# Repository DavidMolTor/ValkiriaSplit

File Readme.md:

# VALKIRIA SPLIT

Completely wireless, split mechanical keyboard based on the nRF52840 microcontroller, with independent wireless operation for each half.

## Introduction

This is a personal project born from my interest in exploring the world of ergonomic mechanical keyboards. After looking at several existing designs, I found that none of them offered exactly what I was looking for, so I decided to design and build my own.

I took a bit of a gamble by choosing a Corne-inspired layout without a dedicated number row, opting for a more minimal design. However, if I find that this layout does not suit my needs, I plan to develop a new version with additional keys.

## Features

 - Completely wireless operation of both sides.

 - Rechargeable and replaceable battery.

 - Hot-swappable chocolate sockets.

 - Full RGB with switchable regulator.

 - Two 1.08" MIP displays.

 - Rotary encoders with push button.

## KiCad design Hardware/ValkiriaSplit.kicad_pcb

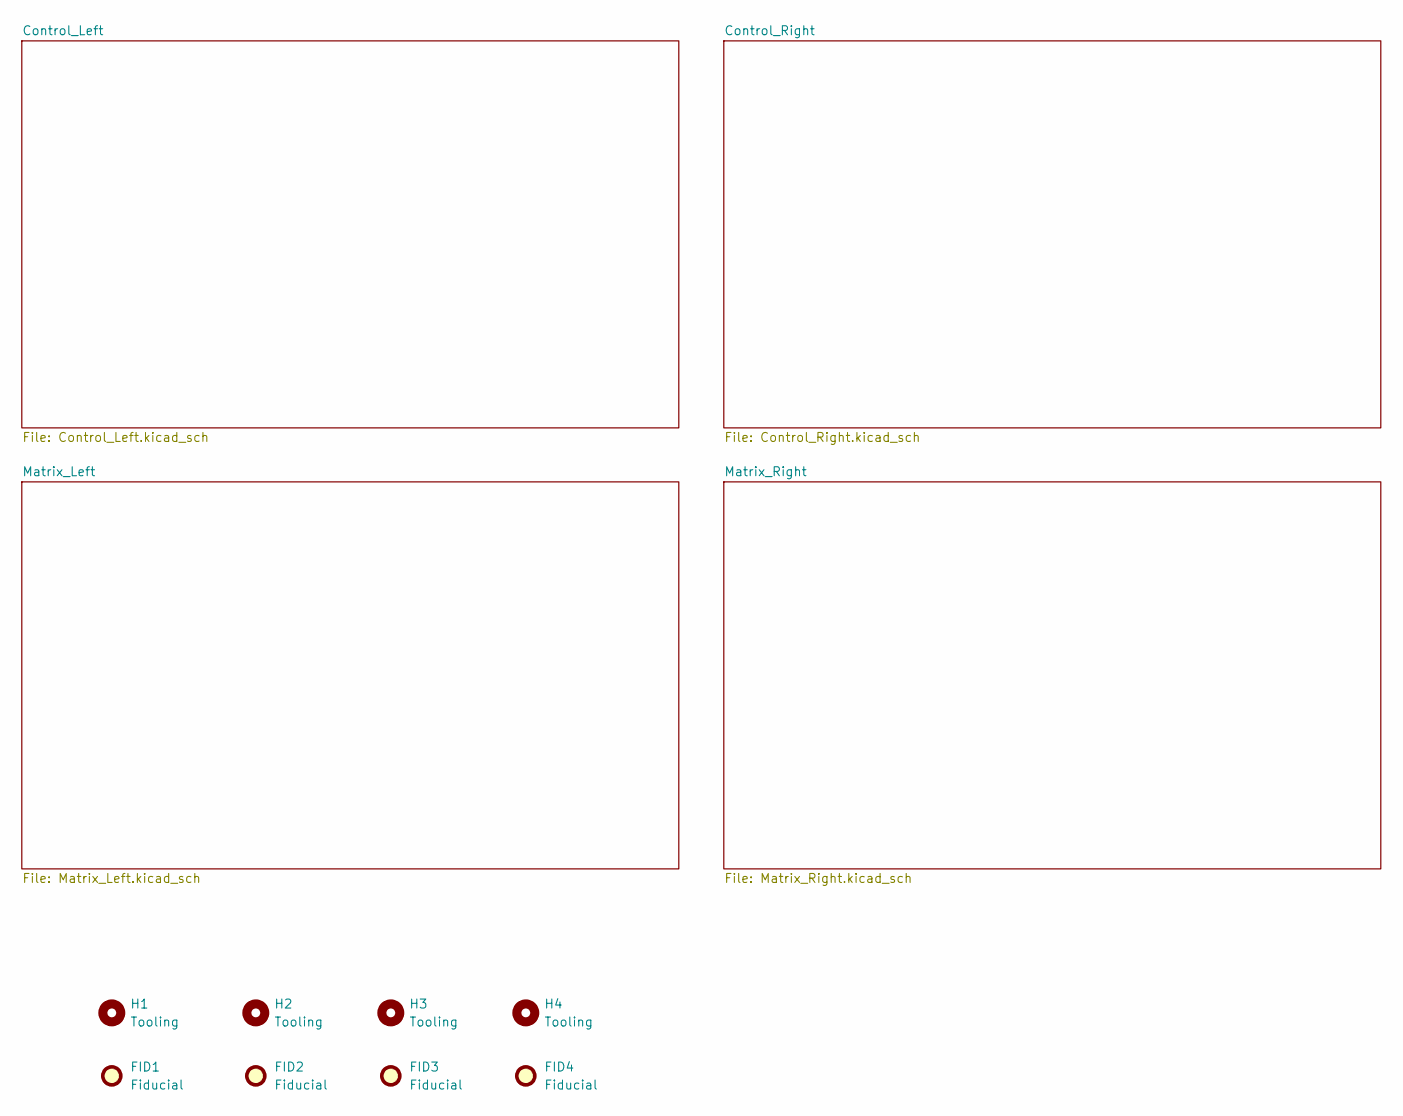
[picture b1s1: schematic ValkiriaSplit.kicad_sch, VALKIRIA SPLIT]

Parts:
FID1, FID2, FID3, FID4: Fiducial; Fiducial_1mm_Mask2mm
H1, H2, H3, H4: Tooling; ToolingHole_1.152mm

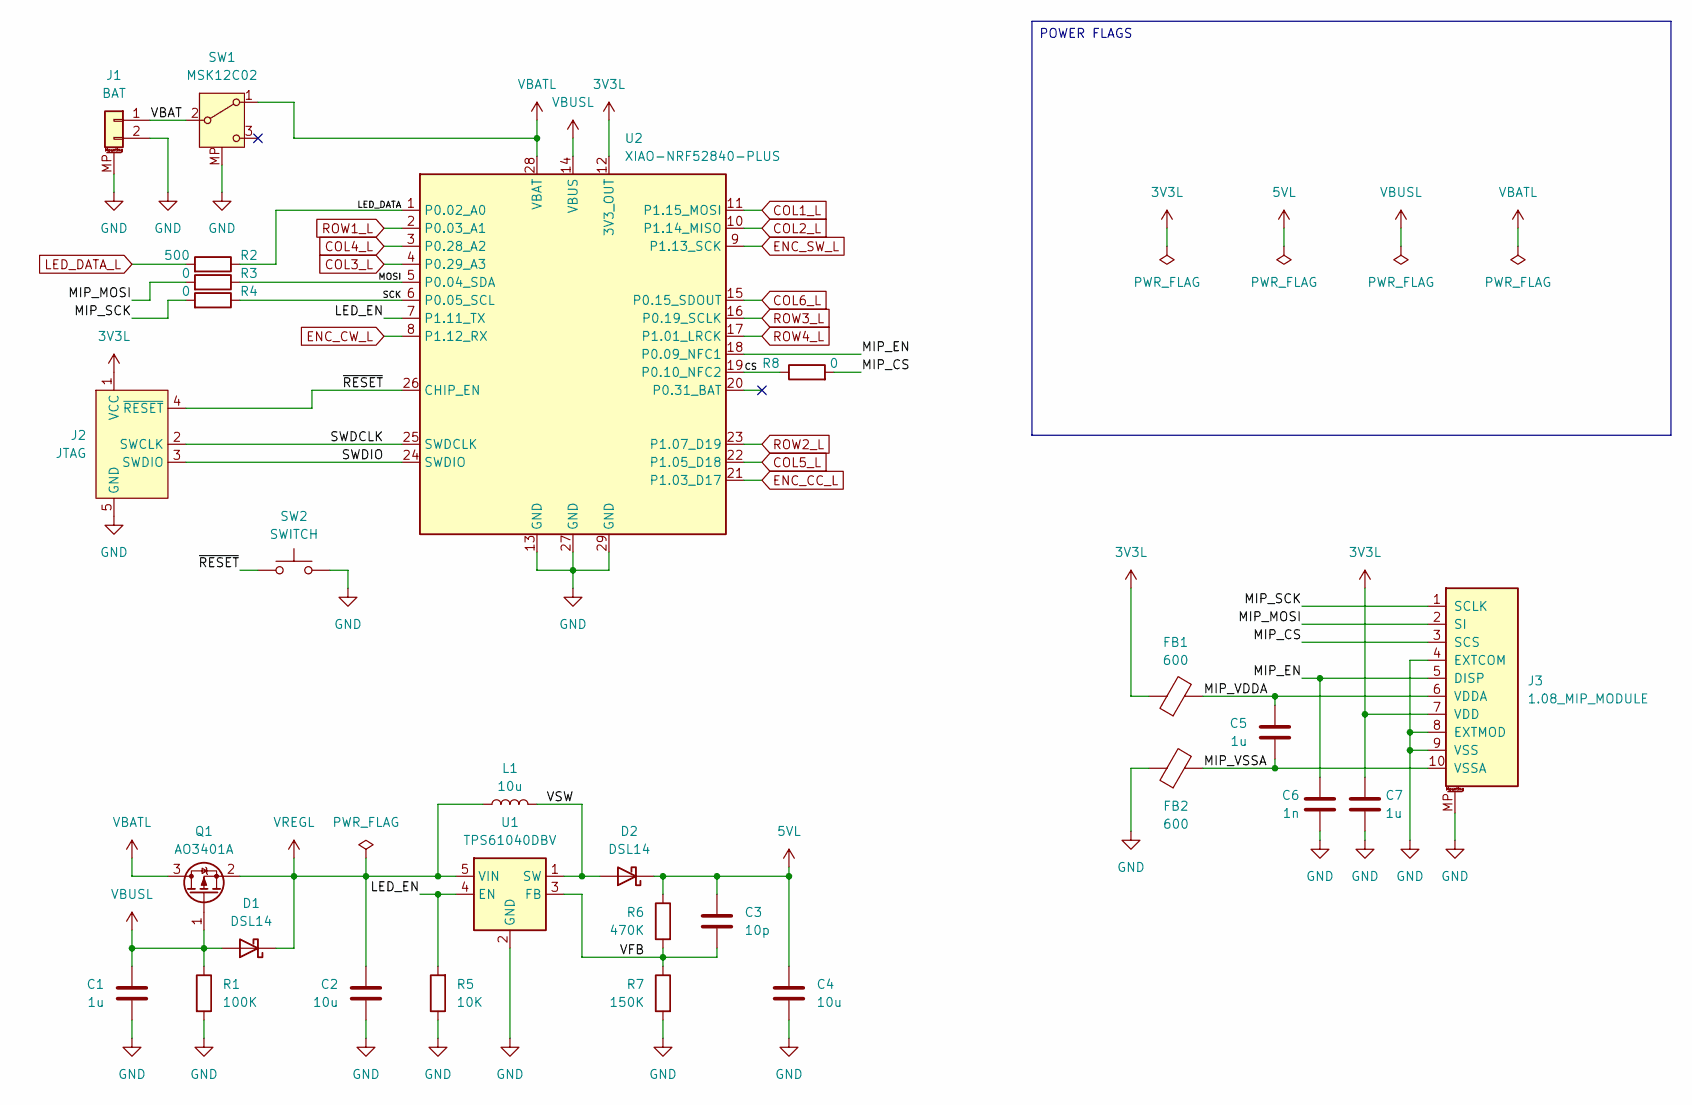
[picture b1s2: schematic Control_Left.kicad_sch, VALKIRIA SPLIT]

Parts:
C1, C5, C7: 1u; C_0603_1608Metric; Manufacturer Part CL10A105KB8NNNC; JLC Part C15849
C2, C4: 10u; C_0603_1608Metric; Manufacturer Part CL10A106MA8NRNC; JLC Part C96446
C3: 10p; C_0603_1608Metric; Manufacturer Part CL10C100JB8NNNC; JLC Part C1634
C6: 1n; C_0603_1608Metric; Manufacturer Part CL10B102KB8NNNC; JLC Part C1588
D1, D2: DSL14; D_SOD-123F; Manufacturer Part DSL14; JLC Part C22466349
FB1, FB2: 600; L_0603_1608Metric; Manufacturer Part GZ1608D601TF; JLC Part C1002
J1: BAT; JST_ZH_1x02_P1.50MM_SMD_HORIZONTAL; Manufacturer Part ZH1.5-2P-WT; JLC Part C722913
J2: JTAG; JTAG_SWD_1X05_1.27MM_COMBO
J3: 1.08_MIP_MODULE; 1.08_MIP_MODULE_TALL; Manufacturer Part AFC07-S10FCC-00; JLC Part C11050
L1: 10u; VLCF4020_MIRROR; Manufacturer Part NRS4018T100MDGJ; JLC Part C222882
Q1: AO3401A; SOT-23; Manufacturer Part AO3401A; JLC Part C15127
R1: 100K; R_0603_1608Metric; Manufacturer Part 0603WAF1003T5E; JLC Part C25803
R2: 500; R_0603_1608Metric; Manufacturer Part 0603WAF0000T5E; JLC Part C21189
R3, R4, R8: 0; R_0603_1608Metric; Manufacturer Part 0603WAF0000T5E; JLC Part C21189
R5: 10K; R_0603_1608Metric; Manufacturer Part 0603WAF1002T5E; JLC Part 0603WAF1002T5E
R6: 470K; R_0603_1608Metric; Manufacturer Part 0603WAF4703T5E; JLC Part C23178
R7: 150K; R_0603_1608Metric; Manufacturer Part 0603WAF1503T5E; JLC Part C22807
SW1: MSK12C02; Manufacturer Part MSK12C02-HB; JLC Part C431541
SW2: SWITCH; SW_SPST_TS-1088-xR020; Manufacturer Part TS-1088-AR02016; JLC Part C720477
U1: TPS61040DBV; SOT-23-5; Manufacturer Part TPS61040DBVR; JLC Part C7722
U2: XIAO-NRF52840-PLUS; XIAO-NRF52840-PLUS-SMD-EDGE

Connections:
3V3L: C7.1, FB1.1, J2.1 (VCC), J3.7 (VDD), U2.12 (3V3_OUT)
5VL: C3.1, C4.1, D2.1 (K), R6.1; also elsewhere on the board
/Control_Left/CS: R8.1, U2.19 (P0.10_NFC2)
/Control_Left/LED_DATA: R2.1, U2.1 (P0.02_A0)
/Control_Left/LED_EN: R5.2, U1.4 (EN), U2.7 (P1.11_TX)
/Control_Left/MIP_CS: J3.3 (SCS), R8.2
/Control_Left/MIP_EN: C6.1, J3.5 (DISP), U2.18 (P0.09_NFC1)
/Control_Left/MIP_MOSI: J3.2 (SI), R3.2
/Control_Left/MIP_SCK: J3.1 (SCLK), R4.2
/Control_Left/MIP_VDDA: C5.1, FB1.2, J3.6 (VDDA)
/Control_Left/MIP_VSSA: C5.2, FB2.2, J3.10 (VSSA)
/Control_Left/MOSI: R3.1, U2.5 (P0.04_SDA)
/Control_Left/SCK: R4.1, U2.6 (P0.05_SCL)
/Control_Left/SWDCLK: J2.2 (SWCLK), U2.25 (SWDCLK)
/Control_Left/SWDIO: J2.3 (SWDIO), U2.24 (SWDIO)
/Control_Left/VBAT: J1.1, SW1.2 (B)
/Control_Left/VFB: C3.2, R6.2, R7.1, U1.3 (FB)
/Control_Left/VSW: D2.2 (A), L1.2, U1.1 (SW)
/Control_Left/~RESET: J2.4 (~RESET), SW2.1, U2.26 (CHIP_EN)
COL1_L: U2.11 (P1.15_MOSI); also elsewhere on the board
COL2_L: U2.10 (P1.14_MISO); also elsewhere on the board
COL3_L: U2.4 (P0.29_A3); also elsewhere on the board
COL4_L: U2.3 (P0.28_A2); also elsewhere on the board
COL5_L: U2.22 (P1.05_D18); also elsewhere on the board
COL6_L: U2.15 (P0.15_SDOUT); also elsewhere on the board
ENC_CC_L: U2.21 (P1.03_D17); also elsewhere on the board
ENC_CW_L: U2.8 (P1.12_RX); also elsewhere on the board
ENC_SW_L: U2.9 (P1.13_SCK); also elsewhere on the board
GND: C1.2, C2.2, C4.2, C6.2, C7.2, FB2.1, J1.2, J1.MP (MountPin), J2.5 (GND), J3.4 (EXTCOM), J3.8 (EXTMOD), J3.9 (VSS), J3.MP, R1.2, R5.1, R7.2, SW1.MP, SW2.2, U1.2 (GND), U2.13 (GND), U2.27 (GND), U2.29 (GND); also elsewhere on the board
LED_DATA_L: R2.2; also elsewhere on the board
ROW1_L: U2.2 (P0.03_A1); also elsewhere on the board
ROW2_L: U2.23 (P1.07_D19); also elsewhere on the board
ROW3_L: U2.16 (P0.19_SCLK); also elsewhere on the board
ROW4_L: U2.17 (P1.01_LRCK); also elsewhere on the board
VBATL: Q1.3 (D), SW1.1 (A), U2.28 (VBAT)
VBUSL: C1.1, D1.2 (A), Q1.1 (G), R1.1, U2.14 (VBUS)
VREGL: C2.1, D1.1 (K), L1.1, Q1.2 (S), U1.5 (VIN)

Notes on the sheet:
POWER FLAGS

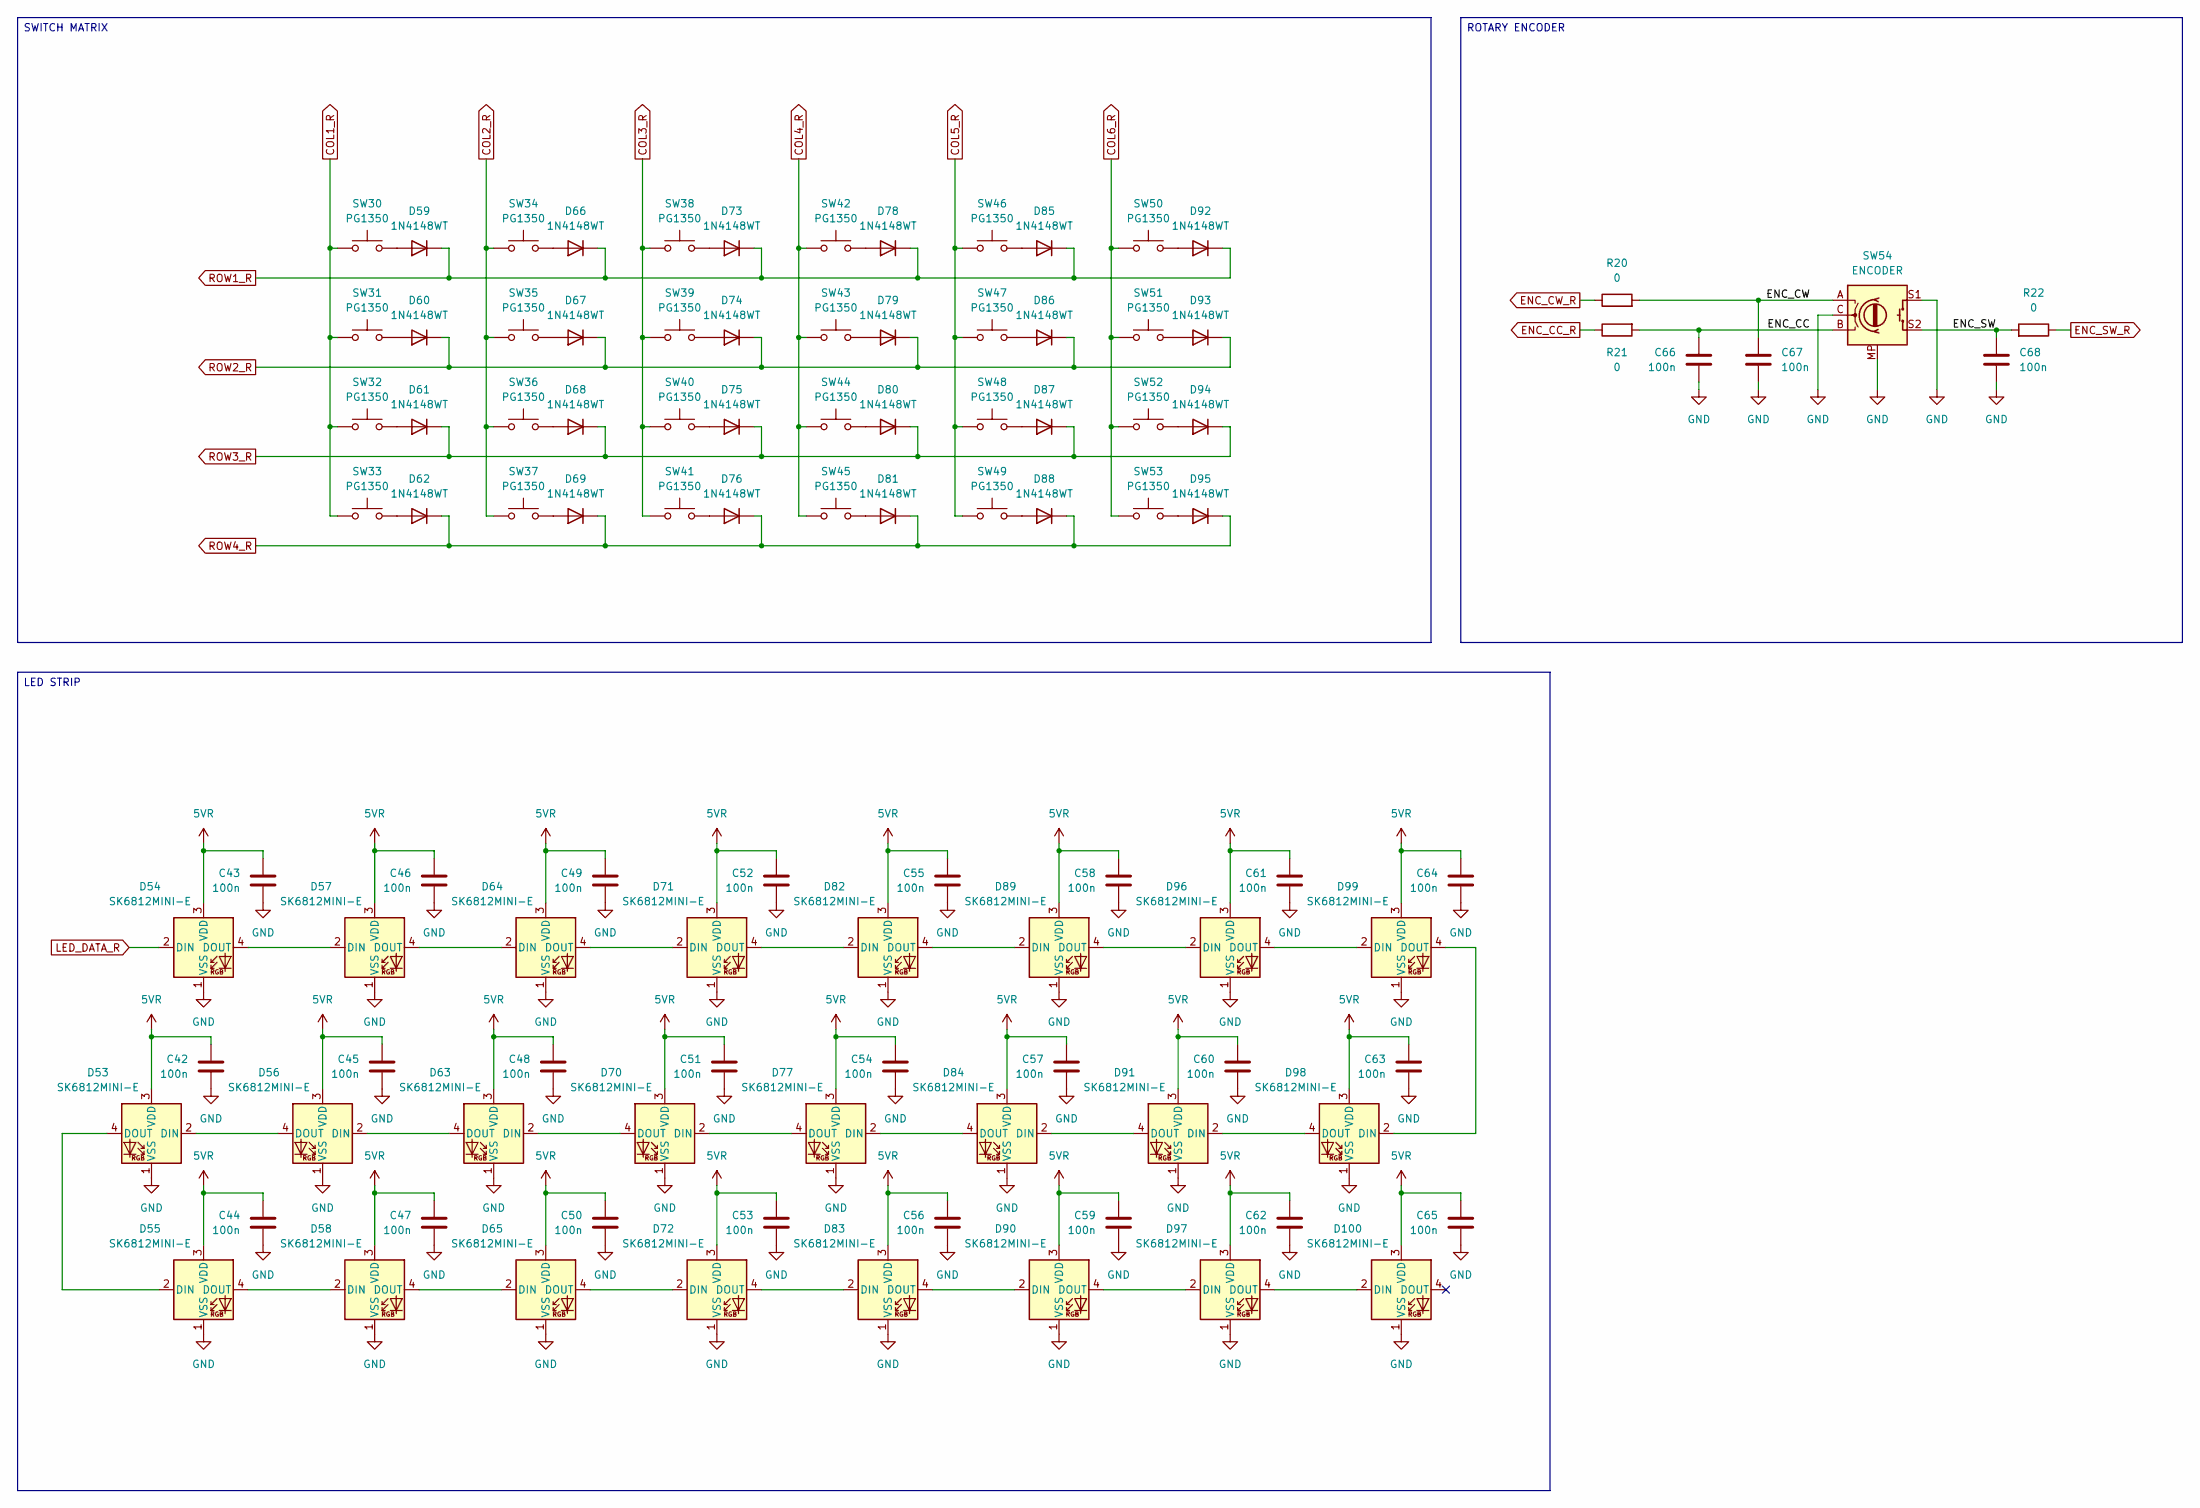
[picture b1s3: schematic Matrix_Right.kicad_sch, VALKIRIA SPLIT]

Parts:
C42, C43, C44, C45, C46, C47, C48, C49, C50, C51, C52, C53, C54, C55, C56, C57, C58, C59, C60, C61, C62, C63, C64, C65, C66, C67, C68: 100n; C_0603_1608Metric; Manufacturer Part CC0603KRX7R9BB104; JLC Part C14663
D53, D54, D55, D56, D57, D58, D63, D64, D65, D70, D71, D72, D77, D82, D83, D84, D89, D90, D91, D96, D97, D98, D99, D100: SK6812MINI-E; LED_SK6812MINI-E_3.2x2.8mm_P1.5mm_ReverseMount; Manufacturer Part SK6812MINI-E; JLC Part C5149201
D59, D60, D61, D62, D66, D67, D68, D69, D73, D74, D75, D76, D78, D79, D80, D81, D85, D86, D87, D88, D92, D93, D94, D95: 1N4148WT; D_SOD-523; Manufacturer Part 1N4148WT; JLC Part C7420320
R20, R21, R22: 0; R_0603_1608Metric; Manufacturer Part 0603WAF0000T5E; JLC Part C21189
SW30, SW31, SW32, SW33, SW34, SW35, SW36, SW37, SW38, SW39, SW40, SW41, SW42, SW43, SW44, SW45, SW46, SW47, SW48, SW49, SW50, SW51, SW52, SW53: PG1350; PG1350_1.00u_PCB_TIGHT; Manufacturer Part CPG135001S30; JLC Part C5333465
SW54: ENCODER; ALPS_EC11J_ENCODER; Manufacturer Part EC11J1525402; JLC Part C209762

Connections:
5VR: C42.1, C43.1, C44.1, C45.1, C46.1, C47.1, C48.1, C49.1, C50.1, C51.1, C52.1, C53.1, C54.1, C55.1, C56.1, C57.1, C58.1, C59.1, C60.1, C61.1, C62.1, C63.1, C64.1, C65.1, D53.3 (VDD), D54.3 (VDD), D55.3 (VDD), D56.3 (VDD), D57.3 (VDD), D58.3 (VDD), D63.3 (VDD), D64.3 (VDD), D65.3 (VDD), D70.3 (VDD), D71.3 (VDD), D72.3 (VDD), D77.3 (VDD), D82.3 (VDD), D83.3 (VDD), D84.3 (VDD), D89.3 (VDD), D90.3 (VDD), D91.3 (VDD), D96.3 (VDD), D97.3 (VDD), D98.3 (VDD), D99.3 (VDD), D100.3 (VDD); also elsewhere on the board
/Matrix_Right/ENC_CC: C66.1, R21.2, SW54.B
/Matrix_Right/ENC_CW: C67.1, R20.2, SW54.A
/Matrix_Right/ENC_SW: C68.1, R22.2, SW54.S2
COL1_R: SW30.1, SW31.1, SW32.1, SW33.1; also elsewhere on the board
COL2_R: SW34.1, SW35.1, SW36.1, SW37.1; also elsewhere on the board
COL3_R: SW38.1, SW39.1, SW40.1, SW41.1; also elsewhere on the board
COL4_R: SW42.1, SW43.1, SW44.1, SW45.1; also elsewhere on the board
COL5_R: SW46.1, SW47.1, SW48.1, SW49.1; also elsewhere on the board
COL6_R: SW50.1, SW51.1, SW52.1, SW53.1; also elsewhere on the board
ENC_CC_R: R21.1; also elsewhere on the board
ENC_CW_R: R20.1; also elsewhere on the board
ENC_SW_R: R22.1; also elsewhere on the board
GND: C42.2, C43.2, C44.2, C45.2, C46.2, C47.2, C48.2, C49.2, C50.2, C51.2, C52.2, C53.2, C54.2, C55.2, C56.2, C57.2, C58.2, C59.2, C60.2, C61.2, C62.2, C63.2, C64.2, C65.2, C66.2, C67.2, C68.2, D53.1 (VSS), D54.1 (VSS), D55.1 (VSS), D56.1 (VSS), D57.1 (VSS), D58.1 (VSS), D63.1 (VSS), D64.1 (VSS), D65.1 (VSS), D70.1 (VSS), D71.1 (VSS), D72.1 (VSS), D77.1 (VSS), D82.1 (VSS), D83.1 (VSS), D84.1 (VSS), D89.1 (VSS), D90.1 (VSS), D91.1 (VSS), D96.1 (VSS), D97.1 (VSS), D98.1 (VSS), D99.1 (VSS), D100.1 (VSS), SW54.C, SW54.MP, SW54.S1; also elsewhere on the board
LED_DATA_R: D54.2 (DIN); also elsewhere on the board
unnamed: D53.2 (DIN), D56.4 (DOUT)
unnamed: D53.4 (DOUT), D55.2 (DIN)
unnamed: D54.4 (DOUT), D57.2 (DIN)
unnamed: D55.4 (DOUT), D58.2 (DIN)
unnamed: D56.2 (DIN), D63.4 (DOUT)
unnamed: D57.4 (DOUT), D64.2 (DIN)
unnamed: D58.4 (DOUT), D65.2 (DIN)
unnamed: D59.2 (A), SW30.2
unnamed: D60.2 (A), SW31.2
unnamed: D61.2 (A), SW32.2
unnamed: D62.2 (A), SW33.2
unnamed: D63.2 (DIN), D70.4 (DOUT)
unnamed: D64.4 (DOUT), D71.2 (DIN)
unnamed: D65.4 (DOUT), D72.2 (DIN)
unnamed: D66.2 (A), SW34.2
unnamed: D67.2 (A), SW35.2
unnamed: D68.2 (A), SW36.2
unnamed: D69.2 (A), SW37.2
unnamed: D70.2 (DIN), D77.4 (DOUT)
unnamed: D71.4 (DOUT), D82.2 (DIN)
unnamed: D72.4 (DOUT), D83.2 (DIN)
unnamed: D73.2 (A), SW38.2
unnamed: D74.2 (A), SW39.2
unnamed: D75.2 (A), SW40.2
unnamed: D76.2 (A), SW41.2
unnamed: D77.2 (DIN), D84.4 (DOUT)
unnamed: D78.2 (A), SW42.2
unnamed: D79.2 (A), SW43.2
unnamed: D80.2 (A), SW44.2
unnamed: D81.2 (A), SW45.2
unnamed: D82.4 (DOUT), D89.2 (DIN)
unnamed: D83.4 (DOUT), D90.2 (DIN)
unnamed: D84.2 (DIN), D91.4 (DOUT)
unnamed: D85.2 (A), SW46.2
unnamed: D86.2 (A), SW47.2
unnamed: D87.2 (A), SW48.2
unnamed: D88.2 (A), SW49.2
unnamed: D89.4 (DOUT), D96.2 (DIN)
unnamed: D90.4 (DOUT), D97.2 (DIN)
unnamed: D91.2 (DIN), D98.4 (DOUT)
unnamed: D92.2 (A), SW50.2
unnamed: D93.2 (A), SW51.2
unnamed: D94.2 (A), SW52.2
unnamed: D95.2 (A), SW53.2
unnamed: D96.4 (DOUT), D99.2 (DIN)
unnamed: D98.2 (DIN), D99.4 (DOUT)
unnamed: D97.4 (DOUT), D100.2 (DIN)
ROW1_R: D59.1 (K), D66.1 (K), D73.1 (K), D78.1 (K), D85.1 (K), D92.1 (K); also elsewhere on the board
ROW2_R: D60.1 (K), D67.1 (K), D74.1 (K), D79.1 (K), D86.1 (K), D93.1 (K); also elsewhere on the board
ROW3_R: D61.1 (K), D68.1 (K), D75.1 (K), D80.1 (K), D87.1 (K), D94.1 (K); also elsewhere on the board
ROW4_R: D62.1 (K), D69.1 (K), D76.1 (K), D81.1 (K), D88.1 (K), D95.1 (K); also elsewhere on the board

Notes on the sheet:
SWITCH MATRIX
ROTARY ENCODER
LED STRIP

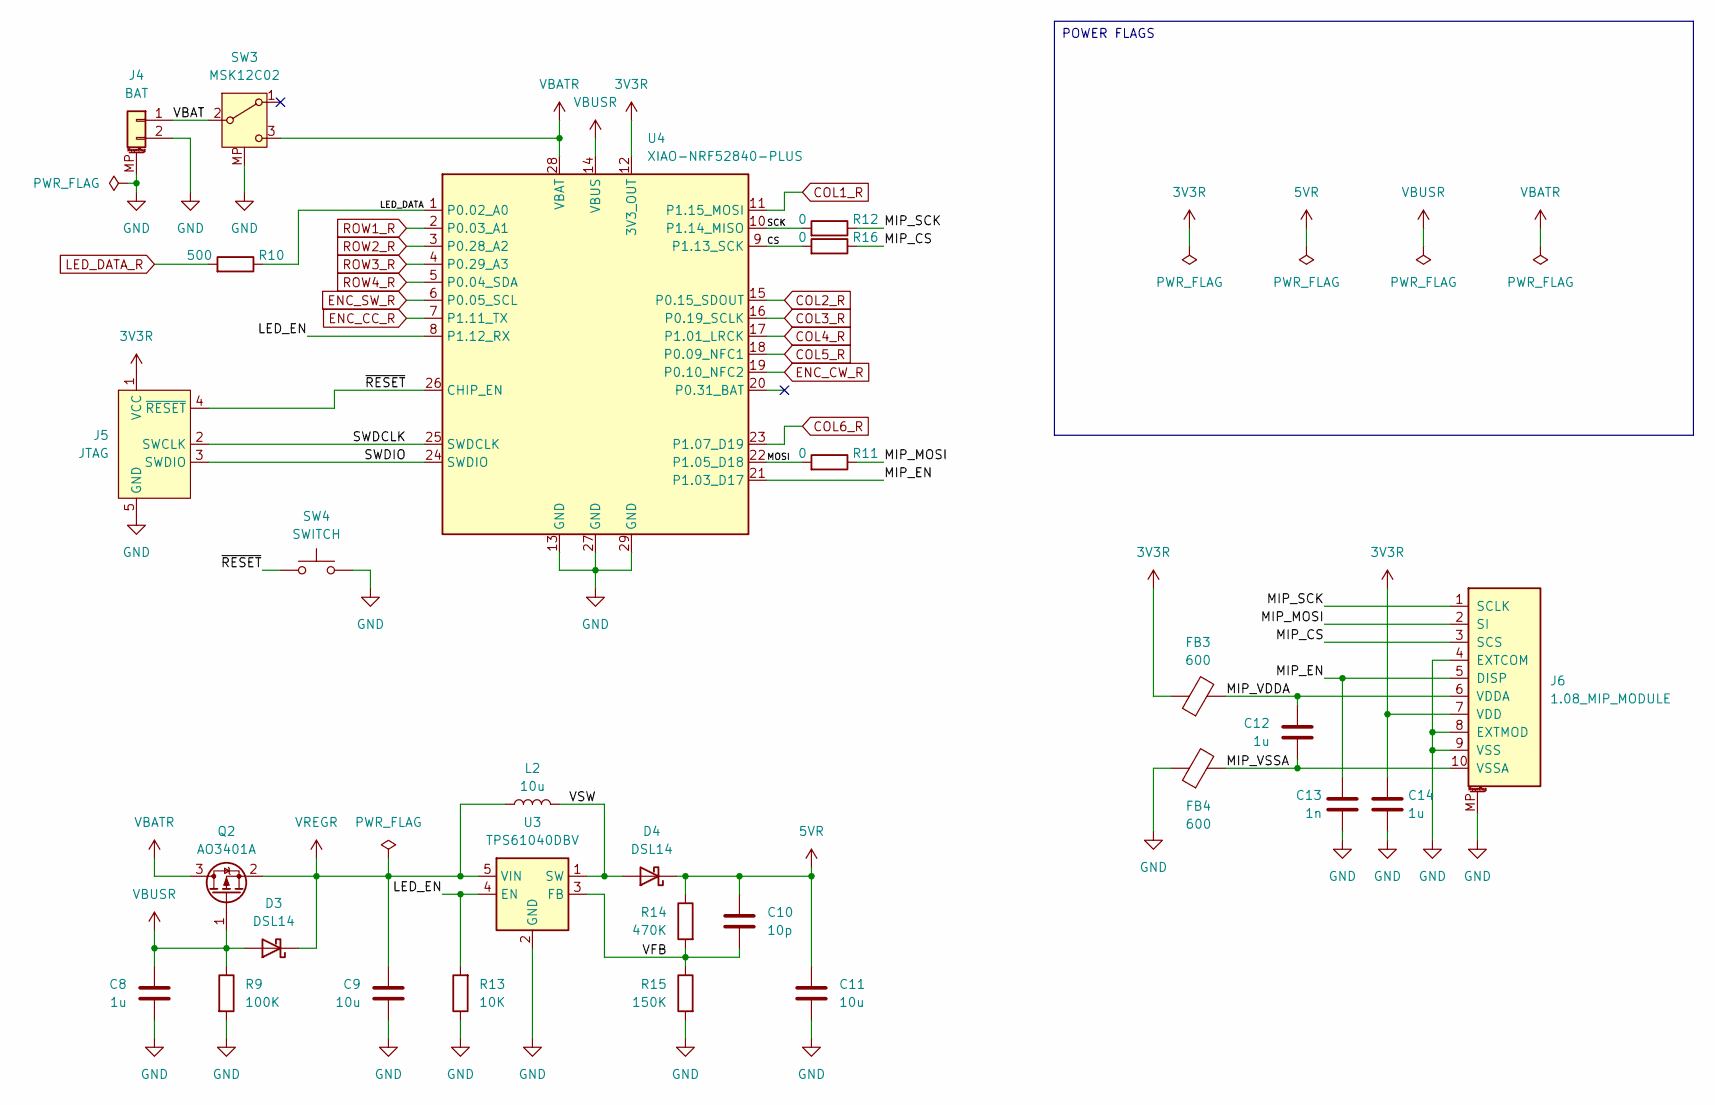
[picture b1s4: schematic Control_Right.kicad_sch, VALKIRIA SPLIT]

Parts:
C8, C12, C14: 1u; C_0603_1608Metric; Manufacturer Part CL10A105KB8NNNC; JLC Part C15849
C9, C11: 10u; C_0603_1608Metric; Manufacturer Part CL10A106MA8NRNC; JLC Part C96446
C10: 10p; C_0603_1608Metric; Manufacturer Part CL10C100JB8NNNC; JLC Part C1634
C13: 1n; C_0603_1608Metric; Manufacturer Part CL10B102KB8NNNC; JLC Part C1588
D3, D4: DSL14; D_SOD-123F; Manufacturer Part DSL14; JLC Part C22466349
FB3, FB4: 600; L_0603_1608Metric; Manufacturer Part GZ1608D601TF; JLC Part C1002
J4: BAT; JST_ZH_1x02_P1.50MM_SMD_HORIZONTAL; Manufacturer Part ZH1.5-2P-WT; JLC Part C722913
J5: JTAG; JTAG_SWD_1X05_1.27MM_COMBO
J6: 1.08_MIP_MODULE; 1.08_MIP_MODULE_TALL; Manufacturer Part AFC07-S10FCC-00; JLC Part C11050
L2: 10u; VLCF4020_MIRROR; Manufacturer Part NRS4018T100MDGJ; JLC Part C222882
Q2: AO3401A; SOT-23; Manufacturer Part AO3401A; JLC Part C15127
R9: 100K; R_0603_1608Metric; Manufacturer Part 0603WAF1003T5E; JLC Part C25803
R10: 500; R_0603_1608Metric; Manufacturer Part 0603WAF0000T5E; JLC Part C21189
R11, R12, R16: 0; R_0603_1608Metric; Manufacturer Part 0603WAF0000T5E; JLC Part C21189
R13: 10K; R_0603_1608Metric; Manufacturer Part 0603WAF1002T5E; JLC Part 0603WAF1002T5E
R14: 470K; R_0603_1608Metric; Manufacturer Part 0603WAF4703T5E; JLC Part C23178
R15: 150K; R_0603_1608Metric; Manufacturer Part 0603WAF1503T5E; JLC Part C22807
SW3: MSK12C02; Manufacturer Part MSK12C02-HB; JLC Part C431541
SW4: SWITCH; SW_SPST_TS-1088-xR020; Manufacturer Part TS-1088-AR02016; JLC Part C720477
U3: TPS61040DBV; SOT-23-5; Manufacturer Part TPS61040DBVR; JLC Part C7722
U4: XIAO-NRF52840-PLUS; XIAO-NRF52840-PLUS-SMD-EDGE

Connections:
3V3R: C14.1, FB3.1, J5.1 (VCC), J6.7 (VDD), U4.12 (3V3_OUT)
5VR: C10.1, C11.1, D4.1 (K), R14.1; also elsewhere on the board
/Control_Right/CS: R16.2, U4.9 (P1.13_SCK)
/Control_Right/LED_DATA: R10.1, U4.1 (P0.02_A0)
/Control_Right/LED_EN: R13.2, U3.4 (EN), U4.8 (P1.12_RX)
/Control_Right/MIP_CS: J6.3 (SCS), R16.1
/Control_Right/MIP_EN: C13.1, J6.5 (DISP), U4.21 (P1.03_D17)
/Control_Right/MIP_MOSI: J6.2 (SI), R11.1
/Control_Right/MIP_SCK: J6.1 (SCLK), R12.1
/Control_Right/MIP_VDDA: C12.1, FB3.2, J6.6 (VDDA)
/Control_Right/MIP_VSSA: C12.2, FB4.2, J6.10 (VSSA)
/Control_Right/MOSI: R11.2, U4.22 (P1.05_D18)
/Control_Right/SCK: R12.2, U4.10 (P1.14_MISO)
/Control_Right/SWDCLK: J5.2 (SWCLK), U4.25 (SWDCLK)
/Control_Right/SWDIO: J5.3 (SWDIO), U4.24 (SWDIO)
/Control_Right/VBAT: J4.1, SW3.2 (B)
/Control_Right/VFB: C10.2, R14.2, R15.1, U3.3 (FB)
/Control_Right/VSW: D4.2 (A), L2.2, U3.1 (SW)
/Control_Right/~RESET: J5.4 (~RESET), SW4.1, U4.26 (CHIP_EN)
COL1_R: U4.11 (P1.15_MOSI); also elsewhere on the board
COL2_R: U4.15 (P0.15_SDOUT); also elsewhere on the board
COL3_R: U4.16 (P0.19_SCLK); also elsewhere on the board
COL4_R: U4.17 (P1.01_LRCK); also elsewhere on the board
COL5_R: U4.18 (P0.09_NFC1); also elsewhere on the board
COL6_R: U4.23 (P1.07_D19); also elsewhere on the board
ENC_CC_R: U4.7 (P1.11_TX); also elsewhere on the board
ENC_CW_R: U4.19 (P0.10_NFC2); also elsewhere on the board
ENC_SW_R: U4.6 (P0.05_SCL); also elsewhere on the board
GND: C8.2, C9.2, C11.2, C13.2, C14.2, FB4.1, J4.2, J4.MP (MountPin), J5.5 (GND), J6.4 (EXTCOM), J6.8 (EXTMOD), J6.9 (VSS), J6.MP, R9.2, R13.1, R15.2, SW3.MP, SW4.2, U3.2 (GND), U4.13 (GND), U4.27 (GND), U4.29 (GND); also elsewhere on the board
LED_DATA_R: R10.2; also elsewhere on the board
ROW1_R: U4.2 (P0.03_A1); also elsewhere on the board
ROW2_R: U4.3 (P0.28_A2); also elsewhere on the board
ROW3_R: U4.4 (P0.29_A3); also elsewhere on the board
ROW4_R: U4.5 (P0.04_SDA); also elsewhere on the board
VBATR: Q2.3 (D), SW3.3 (C), U4.28 (VBAT)
VBUSR: C8.1, D3.2 (A), Q2.1 (G), R9.1, U4.14 (VBUS)
VREGR: C9.1, D3.1 (K), L2.1, Q2.2 (S), U3.5 (VIN)

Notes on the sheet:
POWER FLAGS

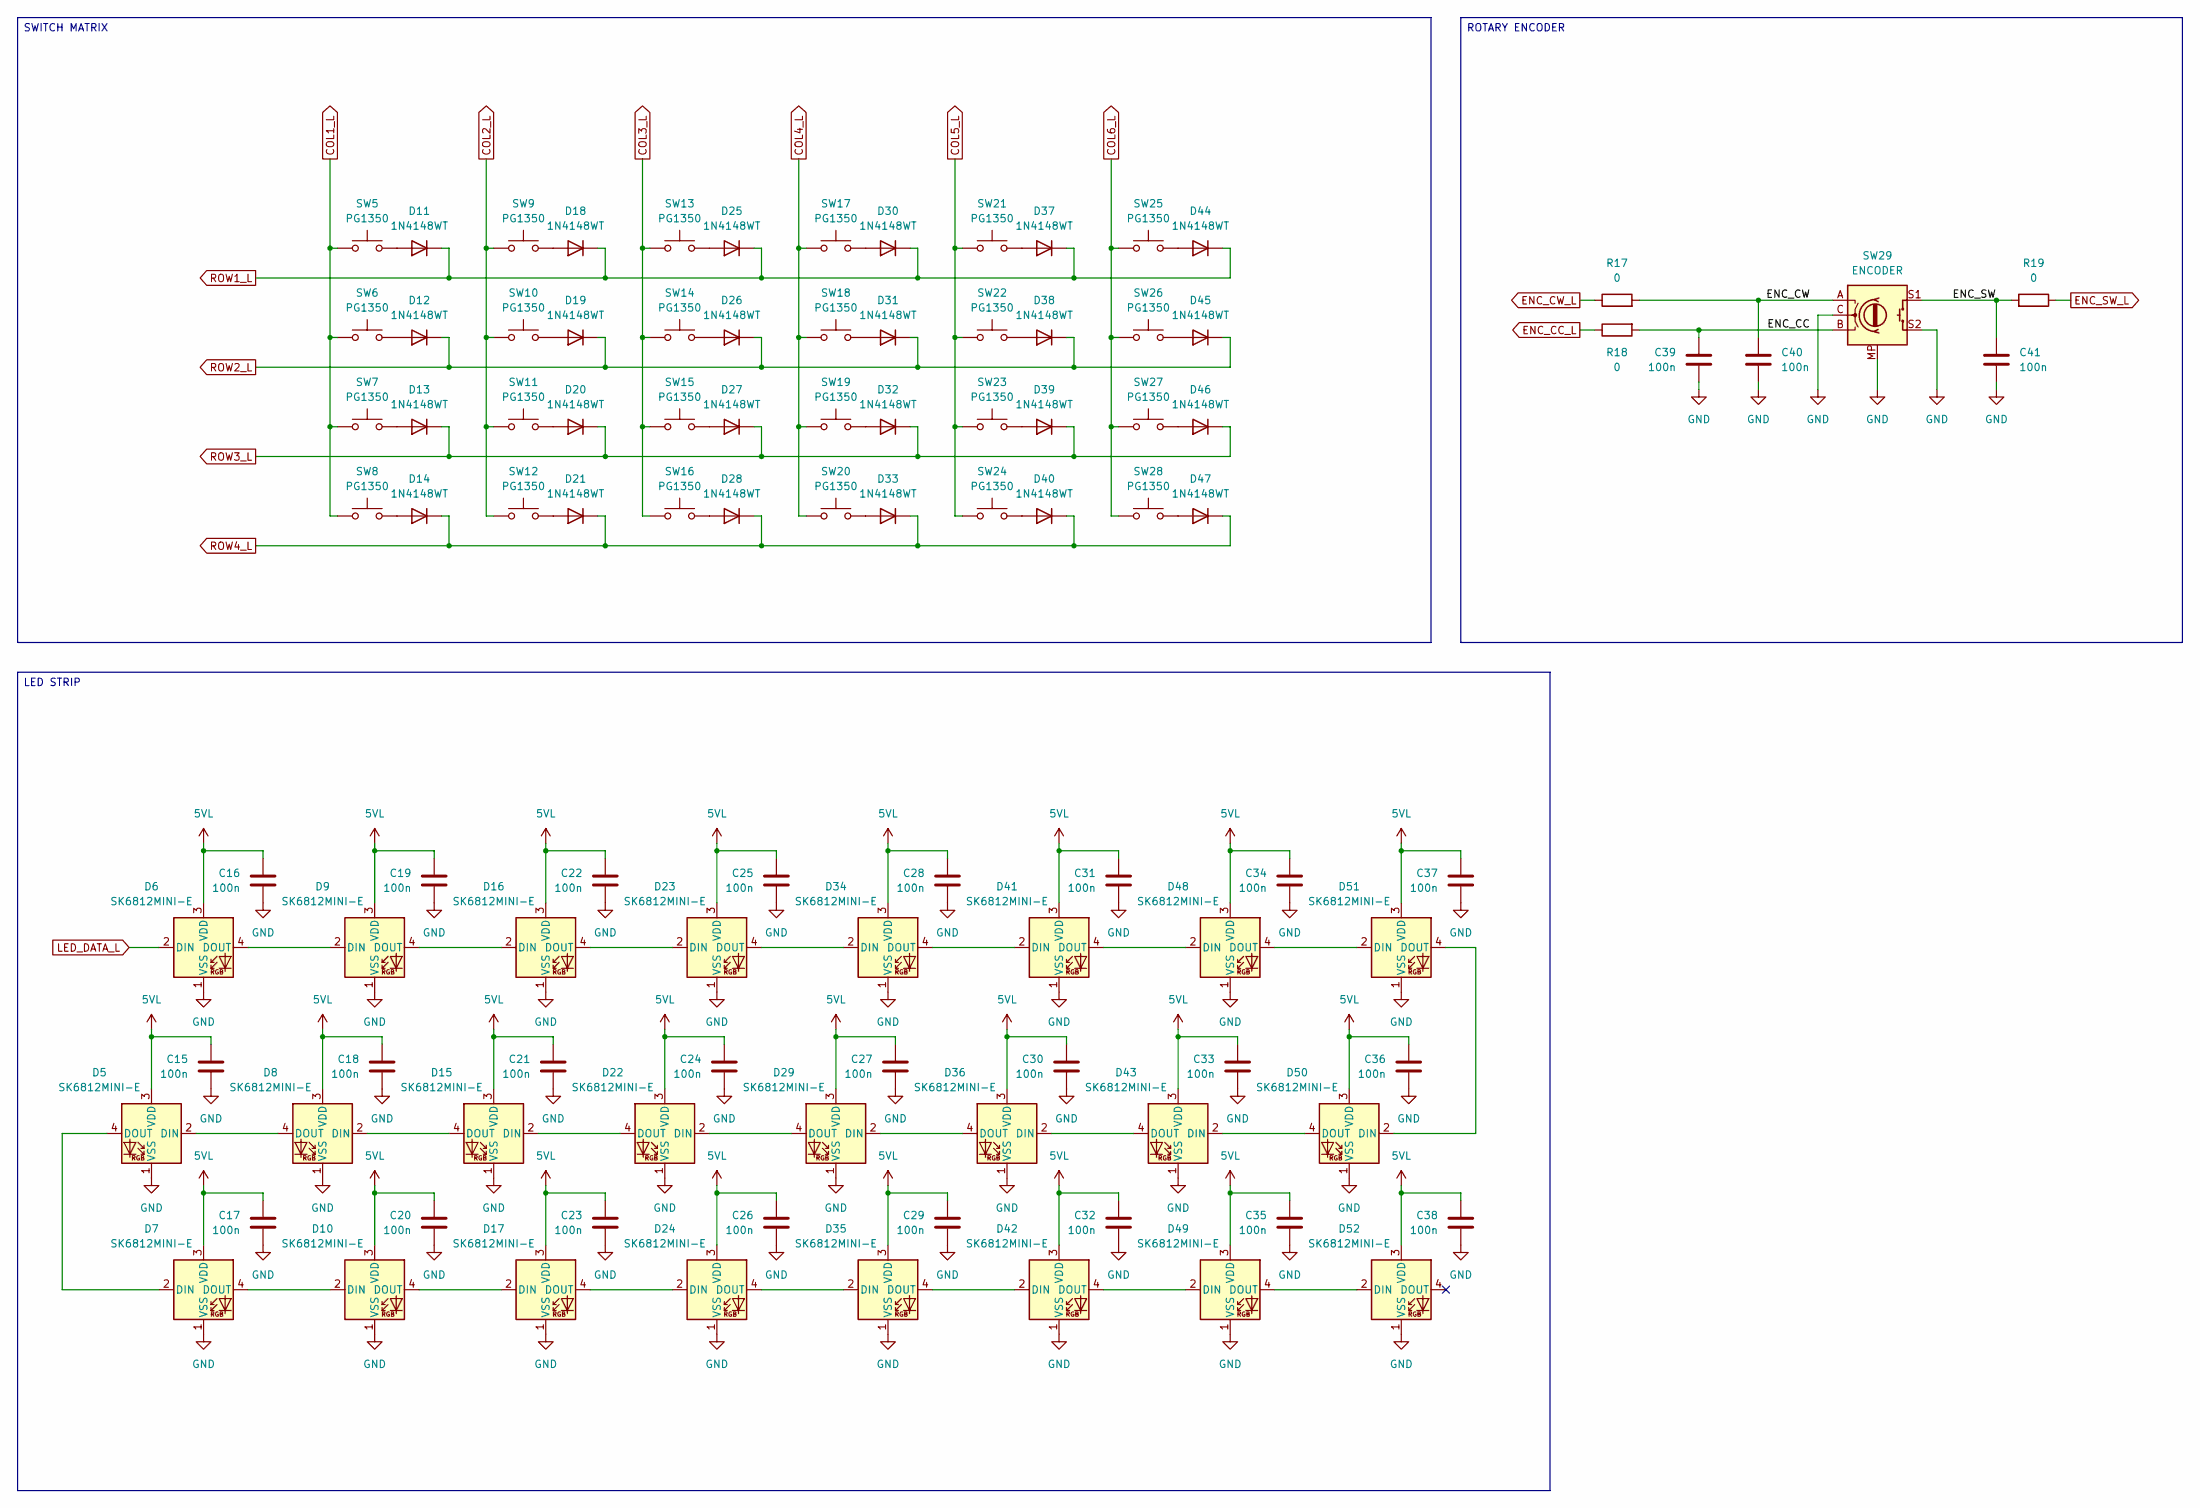
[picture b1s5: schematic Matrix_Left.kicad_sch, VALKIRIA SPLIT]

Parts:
C15, C16, C17, C18, C19, C20, C21, C22, C23, C24, C25, C26, C27, C28, C29, C30, C31, C32, C33, C34, C35, C36, C37, C38, C39, C40, C41: 100n; C_0603_1608Metric; Manufacturer Part CC0603KRX7R9BB104; JLC Part C14663
D5, D6, D7, D8, D9, D10, D15, D16, D17, D22, D23, D24, D29, D34, D35, D36, D41, D42, D43, D48, D49, D50, D51, D52: SK6812MINI-E; LED_SK6812MINI-E_3.2x2.8mm_P1.5mm_ReverseMount; Manufacturer Part SK6812MINI-E; JLC Part C5149201
D11, D12, D13, D14, D18, D19, D20, D21, D25, D26, D27, D28, D30, D31, D32, D33, D37, D38, D39, D40, D44, D45, D46, D47: 1N4148WT; D_SOD-523; Manufacturer Part 1N4148WT; JLC Part C7420320
R17, R18, R19: 0; R_0603_1608Metric; Manufacturer Part 0603WAF0000T5E; JLC Part C21189
SW5, SW6, SW7, SW8, SW9, SW10, SW11, SW12, SW13, SW14, SW15, SW16, SW17, SW18, SW19, SW20, SW21, SW22, SW23, SW24, SW25, SW26, SW27, SW28: PG1350; PG1350_1.00u_PCB_TIGHT; Manufacturer Part CPG135001S30; JLC Part C5333465
SW29: ENCODER; ALPS_EC11J_ENCODER; Manufacturer Part EC11J1525402; JLC Part C209762

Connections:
5VL: C15.1, C16.1, C17.1, C18.1, C19.1, C20.1, C21.1, C22.1, C23.1, C24.1, C25.1, C26.1, C27.1, C28.1, C29.1, C30.1, C31.1, C32.1, C33.1, C34.1, C35.1, C36.1, C37.1, C38.1, D5.3 (VDD), D6.3 (VDD), D7.3 (VDD), D8.3 (VDD), D9.3 (VDD), D10.3 (VDD), D15.3 (VDD), D16.3 (VDD), D17.3 (VDD), D22.3 (VDD), D23.3 (VDD), D24.3 (VDD), D29.3 (VDD), D34.3 (VDD), D35.3 (VDD), D36.3 (VDD), D41.3 (VDD), D42.3 (VDD), D43.3 (VDD), D48.3 (VDD), D49.3 (VDD), D50.3 (VDD), D51.3 (VDD), D52.3 (VDD); also elsewhere on the board
/Matrix_Left/ENC_CC: C39.1, R18.2, SW29.B
/Matrix_Left/ENC_CW: C40.1, R17.2, SW29.A
/Matrix_Left/ENC_SW: C41.1, R19.2, SW29.S1
COL1_L: SW5.1, SW6.1, SW7.1, SW8.1; also elsewhere on the board
COL2_L: SW9.1, SW10.1, SW11.1, SW12.1; also elsewhere on the board
COL3_L: SW13.1, SW14.1, SW15.1, SW16.1; also elsewhere on the board
COL4_L: SW17.1, SW18.1, SW19.1, SW20.1; also elsewhere on the board
COL5_L: SW21.1, SW22.1, SW23.1, SW24.1; also elsewhere on the board
COL6_L: SW25.1, SW26.1, SW27.1, SW28.1; also elsewhere on the board
ENC_CC_L: R18.1; also elsewhere on the board
ENC_CW_L: R17.1; also elsewhere on the board
ENC_SW_L: R19.1; also elsewhere on the board
GND: C15.2, C16.2, C17.2, C18.2, C19.2, C20.2, C21.2, C22.2, C23.2, C24.2, C25.2, C26.2, C27.2, C28.2, C29.2, C30.2, C31.2, C32.2, C33.2, C34.2, C35.2, C36.2, C37.2, C38.2, C39.2, C40.2, C41.2, D5.1 (VSS), D6.1 (VSS), D7.1 (VSS), D8.1 (VSS), D9.1 (VSS), D10.1 (VSS), D15.1 (VSS), D16.1 (VSS), D17.1 (VSS), D22.1 (VSS), D23.1 (VSS), D24.1 (VSS), D29.1 (VSS), D34.1 (VSS), D35.1 (VSS), D36.1 (VSS), D41.1 (VSS), D42.1 (VSS), D43.1 (VSS), D48.1 (VSS), D49.1 (VSS), D50.1 (VSS), D51.1 (VSS), D52.1 (VSS), SW29.C, SW29.MP, SW29.S2; also elsewhere on the board
LED_DATA_L: D6.2 (DIN); also elsewhere on the board
unnamed: D5.2 (DIN), D8.4 (DOUT)
unnamed: D5.4 (DOUT), D7.2 (DIN)
unnamed: D6.4 (DOUT), D9.2 (DIN)
unnamed: D7.4 (DOUT), D10.2 (DIN)
unnamed: D10.4 (DOUT), D17.2 (DIN)
unnamed: D11.2 (A), SW5.2
unnamed: D12.2 (A), SW6.2
unnamed: D13.2 (A), SW7.2
unnamed: D14.2 (A), SW8.2
unnamed: D15.2 (DIN), D22.4 (DOUT)
unnamed: D8.2 (DIN), D15.4 (DOUT)
unnamed: D9.4 (DOUT), D16.2 (DIN)
unnamed: D16.4 (DOUT), D23.2 (DIN)
unnamed: D17.4 (DOUT), D24.2 (DIN)
unnamed: D18.2 (A), SW9.2
unnamed: D19.2 (A), SW10.2
unnamed: D20.2 (A), SW11.2
unnamed: D21.2 (A), SW12.2
unnamed: D22.2 (DIN), D29.4 (DOUT)
unnamed: D23.4 (DOUT), D34.2 (DIN)
unnamed: D24.4 (DOUT), D35.2 (DIN)
unnamed: D25.2 (A), SW13.2
unnamed: D26.2 (A), SW14.2
unnamed: D27.2 (A), SW15.2
unnamed: D28.2 (A), SW16.2
unnamed: D29.2 (DIN), D36.4 (DOUT)
unnamed: D30.2 (A), SW17.2
unnamed: D31.2 (A), SW18.2
unnamed: D32.2 (A), SW19.2
unnamed: D33.2 (A), SW20.2
unnamed: D34.4 (DOUT), D41.2 (DIN)
unnamed: D35.4 (DOUT), D42.2 (DIN)
unnamed: D36.2 (DIN), D43.4 (DOUT)
unnamed: D37.2 (A), SW21.2
unnamed: D38.2 (A), SW22.2
unnamed: D39.2 (A), SW23.2
unnamed: D40.2 (A), SW24.2
unnamed: D41.4 (DOUT), D48.2 (DIN)
unnamed: D42.4 (DOUT), D49.2 (DIN)
unnamed: D43.2 (DIN), D50.4 (DOUT)
unnamed: D44.2 (A), SW25.2
unnamed: D45.2 (A), SW26.2
unnamed: D46.2 (A), SW27.2
unnamed: D47.2 (A), SW28.2
unnamed: D48.4 (DOUT), D51.2 (DIN)
unnamed: D49.4 (DOUT), D52.2 (DIN)
unnamed: D50.2 (DIN), D51.4 (DOUT)
ROW1_L: D11.1 (K), D18.1 (K), D25.1 (K), D30.1 (K), D37.1 (K), D44.1 (K); also elsewhere on the board
ROW2_L: D12.1 (K), D19.1 (K), D26.1 (K), D31.1 (K), D38.1 (K), D45.1 (K); also elsewhere on the board
ROW3_L: D13.1 (K), D20.1 (K), D27.1 (K), D32.1 (K), D39.1 (K), D46.1 (K); also elsewhere on the board
ROW4_L: D14.1 (K), D21.1 (K), D28.1 (K), D33.1 (K), D40.1 (K), D47.1 (K); also elsewhere on the board

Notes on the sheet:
LED STRIP
ROTARY ENCODER
SWITCH MATRIX
